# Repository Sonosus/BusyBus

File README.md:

# BusyBus
[![CC BY-SA 4.0][cc-by-sa-shield]][cc-by-sa]

Bus board getting busy? Running out of sockets and just have a few more modules to connect before your case is full? Enter BusyBus, a tiny 5-socket extension bus board for embiggening your system just that little bit more.

This work is licensed under a
[Creative Commons Attribution-ShareAlike 4.0 International License][cc-by-sa].

[![CC BY-SA 4.0][cc-by-sa-image]][cc-by-sa]

[cc-by-sa]: http://creativecommons.org/licenses/by-sa/4.0/
[cc-by-sa-image]: https://licensebuttons.net/l/by-sa/4.0/88x31.png
[cc-by-sa-shield]: https://img.shields.io/badge/License-CC%20BY--SA%204.0-lightgrey.svg

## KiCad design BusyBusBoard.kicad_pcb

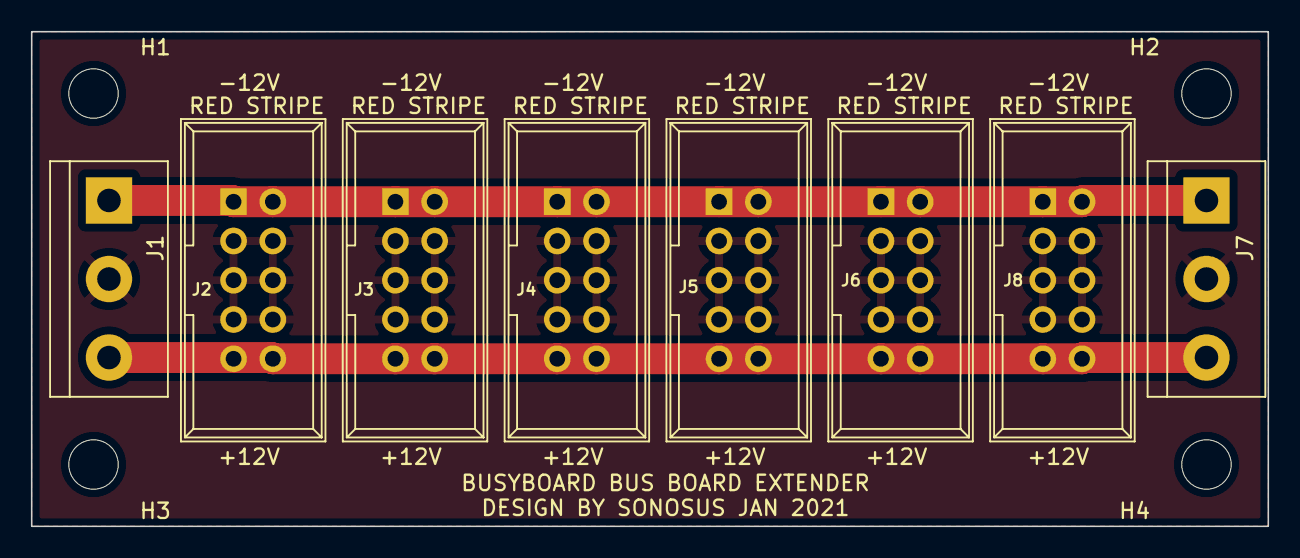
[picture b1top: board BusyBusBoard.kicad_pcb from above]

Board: 2 copper layers, 80.0 x 32.0 mm, 12 parts (0 on the bottom side), 3 nets.

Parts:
H1, H2, H3, H4: MountingHole; MountingHole_3.2mm_M3
J1, J7: BUS CONN; TerminalBlock_bornier-3_P5.08mm
J2, J3, J4, J5, J6, J8: Power Header; Power_Header

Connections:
+12V: J1.3, J2.9, J2.10, J3.9, J3.10, J4.9, J4.10, J5.9, J5.10, J6.9, J6.10, J7.3, J8.9, J8.10
-12V: J1.1, J2.1, J2.2, J3.1, J3.2, J4.1, J4.2, J5.1, J5.2, J6.1, J6.2, J7.1, J8.1, J8.2
GND: J1.2, J2.3, J2.4, J2.5, J2.6, J2.7, J2.8, J3.3, J3.4, J3.5, J3.6, J3.7, J3.8, J4.3, J4.4, J4.5, J4.6, J4.7, J4.8, J5.3, J5.4, J5.5, J5.6, J5.7, J5.8, J6.3, J6.4, J6.5, J6.6, J6.7, J6.8, J7.2, J8.3, J8.4, J8.5, J8.6, J8.7, J8.8

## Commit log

2022-01-31 done
2022-01-31 gerber
